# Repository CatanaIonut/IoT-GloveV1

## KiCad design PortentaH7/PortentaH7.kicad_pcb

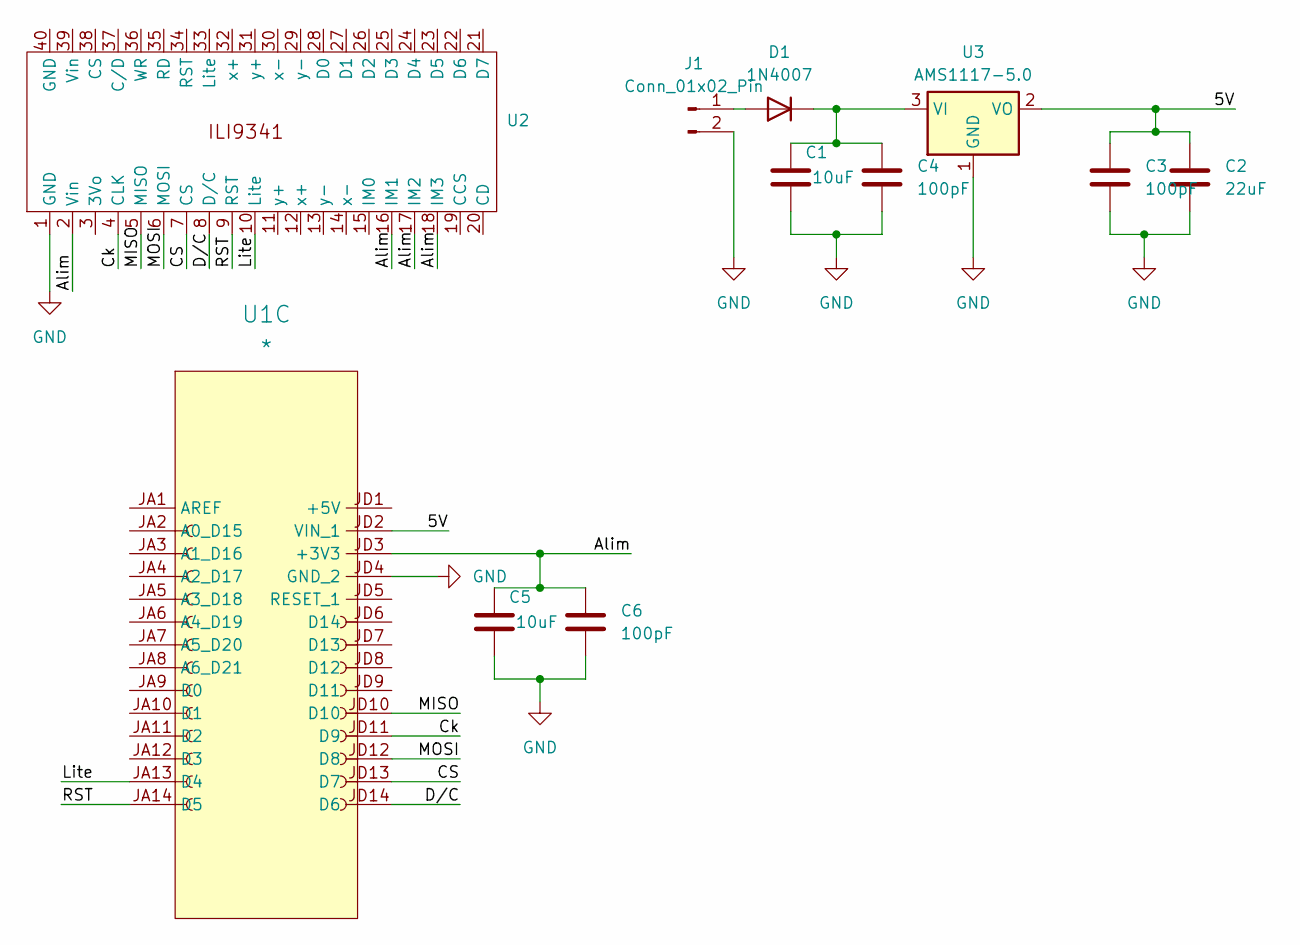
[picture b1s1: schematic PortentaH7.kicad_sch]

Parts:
C1, C5: 10uF; C_1206_3216Metric_Pad1.33x1.80mm_HandSolder
C2: 22uF; C_1206_3216Metric_Pad1.33x1.80mm_HandSolder
C3, C4, C6: 100pF; C_1206_3216Metric_Pad1.33x1.80mm_HandSolder
D1: 1N4007; D_DO-41_SOD81_P10.16mm_Horizontal
J1: Conn_01x02_Pin; PinHeader_1x02_P2.54mm_Vertical
U1: *; PortentaH7(ABX00042)
U2: ILI9341
U3: AMS1117-5.0; SOT-223-3_TabPin2

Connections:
/5V: C2.1, C3.1, U1.JD2 (VIN_1), U3.2 (VO)
/Alim: C5.1, C6.1, U1.JD3 (+3V3), U2.2 (Vin), U2.16 (IM1), U2.17 (IM2), U2.18 (IM3)
/CS: U1.JD13 (D7), U2.7 (CS)
/Ck: U1.JD11 (D9), U2.4 (CLK)
/D/C: U1.JD14 (D6), U2.8 (D/C)
/Lite: U1.JA13 (D4), U2.10 (Lite)
/MISO: U1.JD10 (D10), U2.5 (MISO)
/MOSI: U1.JD12 (D8), U2.6 (MOSI)
/RST: U1.JA14 (D5), U2.9 (RST)
GND: C1.2, C2.2, C3.2, C4.2, C5.2, C6.2, J1.2, U1.JD4 (GND_2), U2.1 (GND), U3.1 (GND)
unnamed: D1.2 (A), J1.1
unnamed: C1.1, C4.1, D1.1 (K), U3.3 (VI)

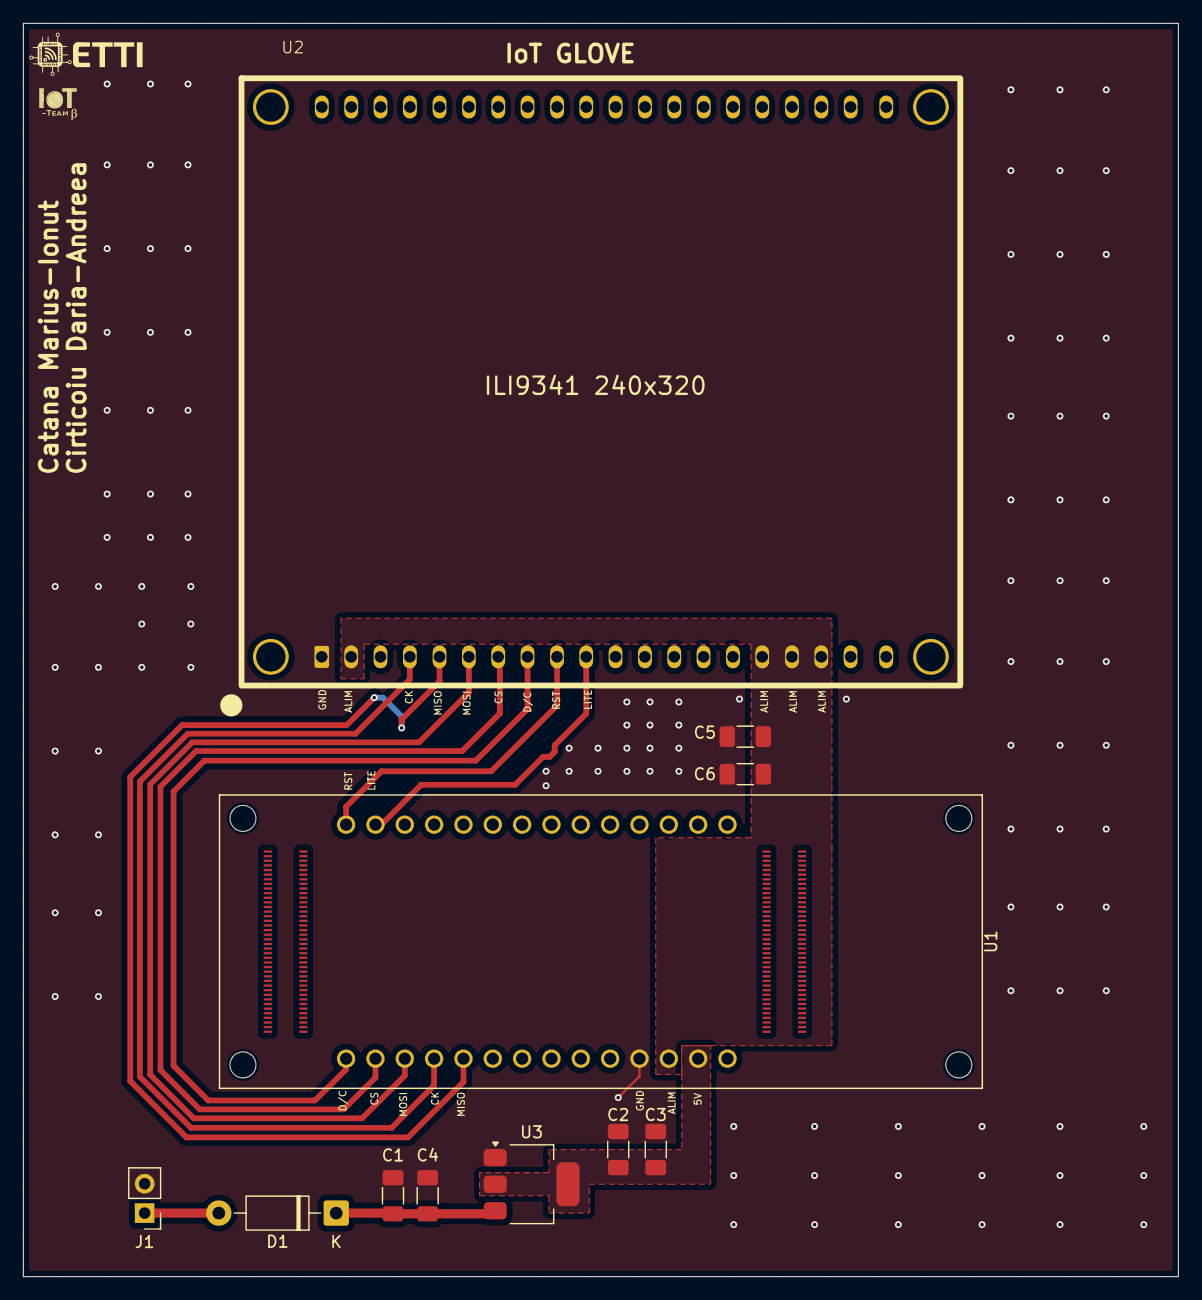
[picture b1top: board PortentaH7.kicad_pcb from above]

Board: 2 copper layers, 100.0 x 108.5 mm, 11 parts (0 on the bottom side), 12 nets.

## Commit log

2025-09-01 Test
2025-09-01 sadsa
2025-09-02 Wifi- conn
2025-09-02 Am rezolvat tot
2025-12-21 asdsad
2025-12-22 Add files via upload
    Utilized schematic and PCB design in KiCad to develop two custom electronic boards: one for the glove with Nicla Sense Me and sensors and the other one for Portenta and screen.
2026-03-23 Add SparkFun Displacement Sensor library
2026-03-23 Integrated flex sensor with I2C and BLE support
